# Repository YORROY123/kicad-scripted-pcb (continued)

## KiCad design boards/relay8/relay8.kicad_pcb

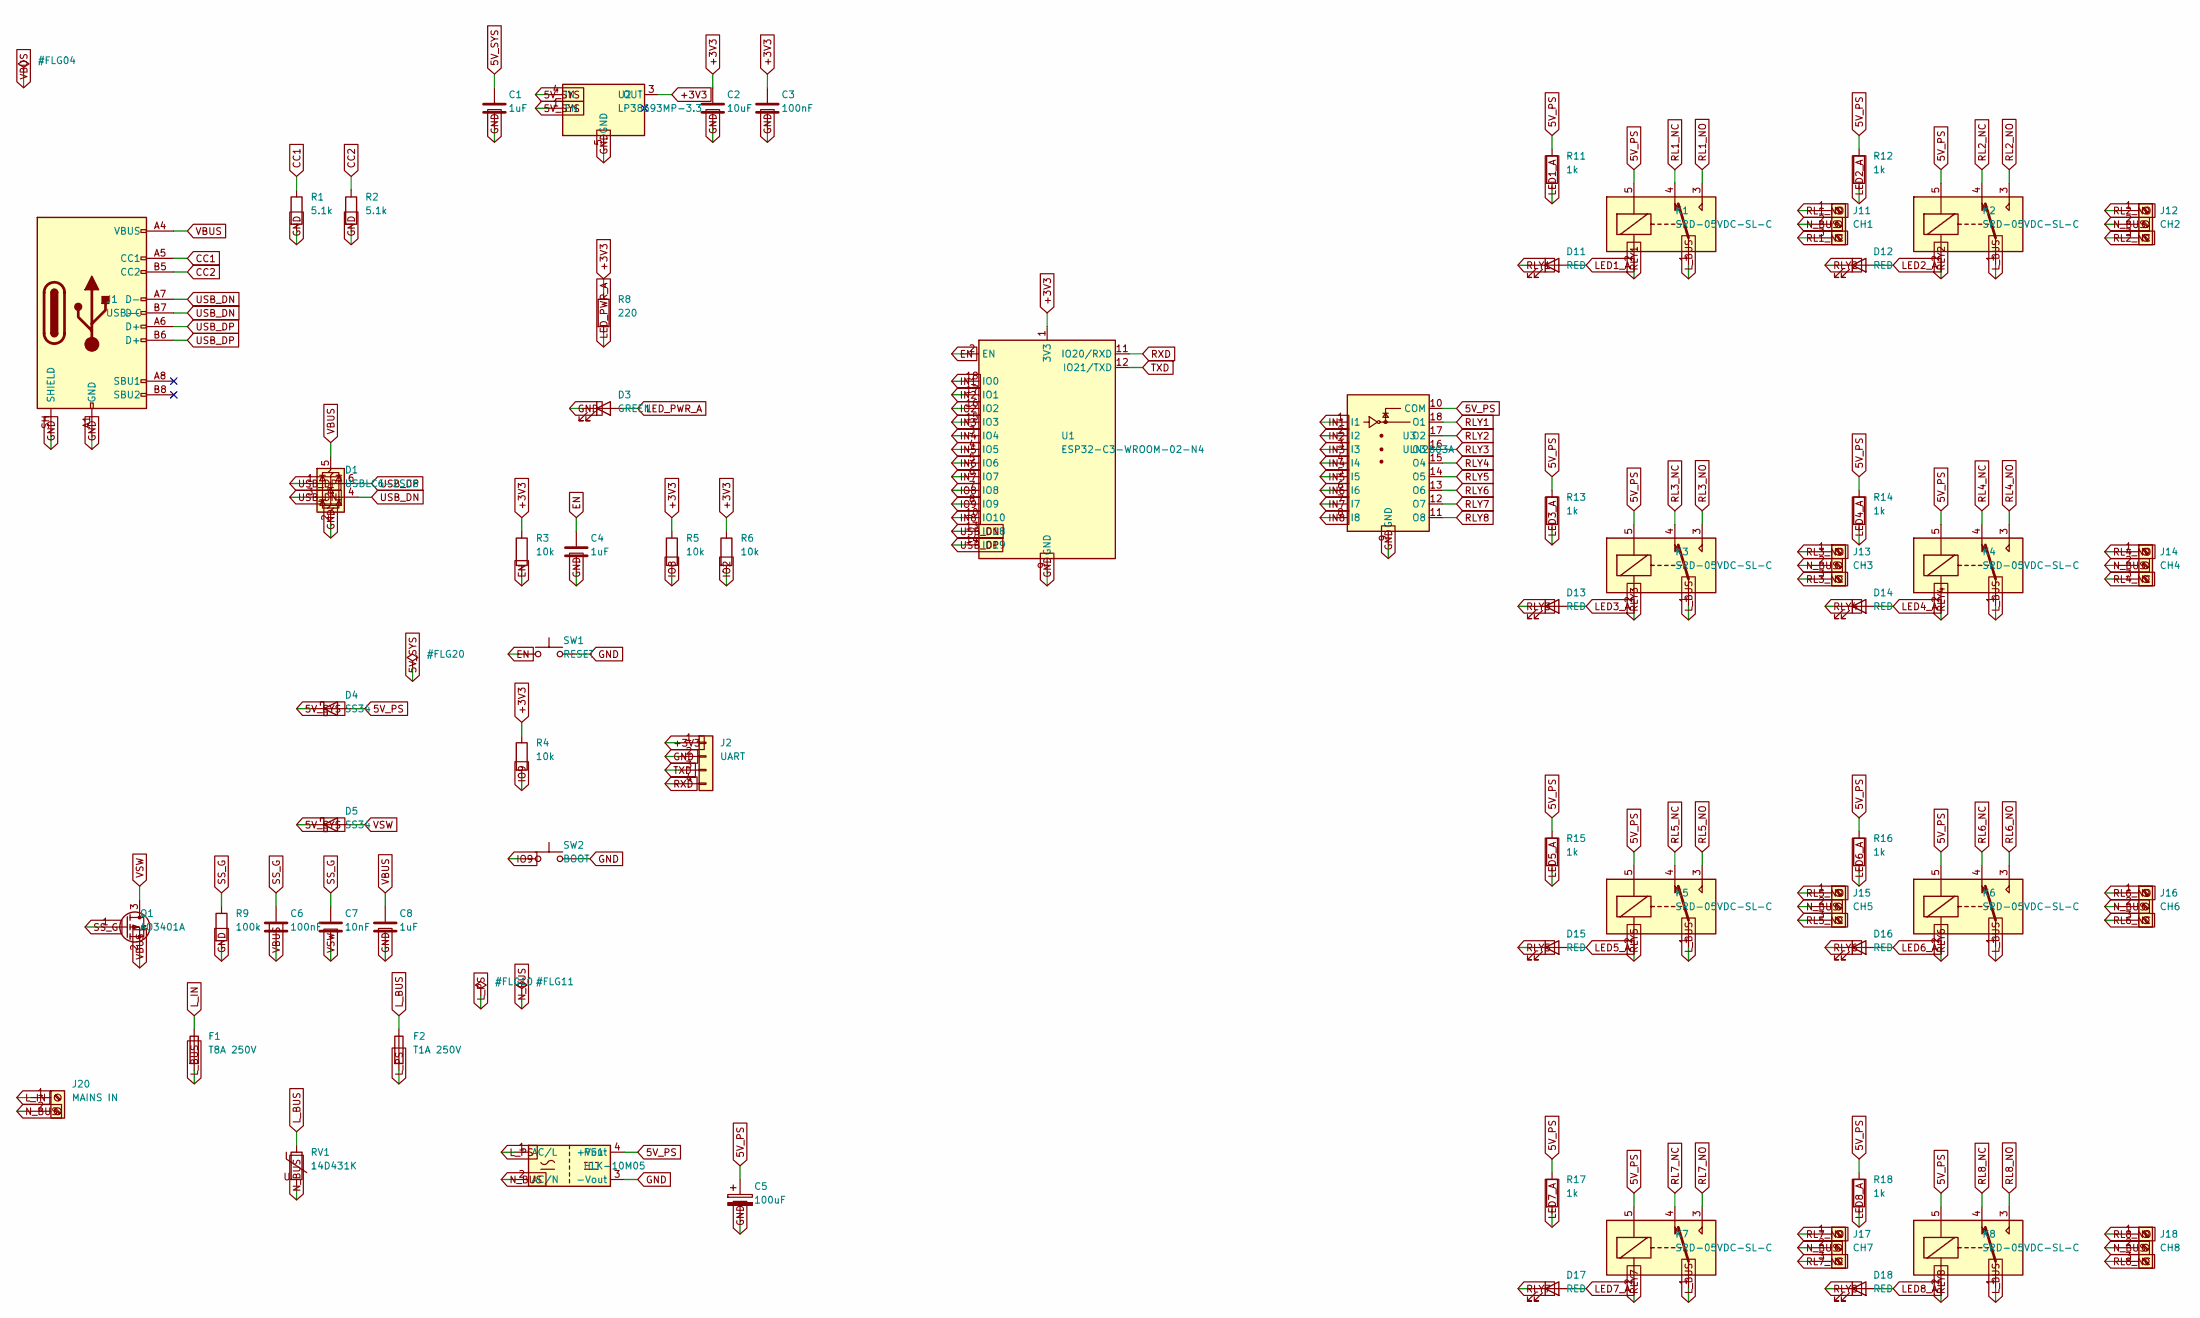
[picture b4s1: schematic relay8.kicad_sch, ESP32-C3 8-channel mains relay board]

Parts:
C1, C4, C8: 1uF; C_0402_1005Metric
C2: 10uF; C_0805_2012Metric
C3, C6: 100nF; C_0402_1005Metric
C5: 100uF; CP_Elec_6.3x7.7
C7: 10nF; C_0402_1005Metric
D1: USBLC6-2SC6; SOT-23-6
D3: GREEN; LED_0805_2012Metric
D4, D5: SS34; D_SMA
D11, D12, D13, D14, D15, D16, D17, D18: RED; LED_0805_2012Metric
F1: T8A 250V; Fuseholder_Clip-5x20mm_Keystone_3517_Inline_P23.11x6.76mm_D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
F2: T1A 250V; Fuseholder_TR5_Littelfuse_No560_No460
J1: USB-C; USB_C_Receptacle_HRO_TYPE-C-31-M-12
J2: UART; PinHeader_1x04_P2.54mm_Vertical
J11: CH1; TerminalBlock_MetzConnect_Type171_RT13703HBWC_1x03_P7.50mm_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
J12: CH2; TerminalBlock_MetzConnect_Type171_RT13703HBWC_1x03_P7.50mm_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
J13: CH3; TerminalBlock_MetzConnect_Type171_RT13703HBWC_1x03_P7.50mm_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
J14: CH4; TerminalBlock_MetzConnect_Type171_RT13703HBWC_1x03_P7.50mm_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
J15: CH5; TerminalBlock_MetzConnect_Type171_RT13703HBWC_1x03_P7.50mm_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
J16: CH6; TerminalBlock_MetzConnect_Type171_RT13703HBWC_1x03_P7.50mm_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
J17: CH7; TerminalBlock_MetzConnect_Type171_RT13703HBWC_1x03_P7.50mm_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
J18: CH8; TerminalBlock_MetzConnect_Type171_RT13703HBWC_1x03_P7.50mm_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
J20: MAINS IN; TerminalBlock_MetzConnect_Type171_RT13702HBWC_1x02_P7.50mm_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
K1, K2, K3, K4, K5, K6, K7, K8: SRD-05VDC-SL-C; Relay_SPDT_SANYOU_SRD_Series_Form_C
PS1: HLK-10M05; Converter_ACDC_Hi-Link_HLK-10Mxx
Q1: AO3401A; SOT-23
R1, R2: 5.1k; R_0402_1005Metric
R3, R4, R5, R6: 10k; R_0402_1005Metric
R8: 220; R_0402_1005Metric
R9: 100k; R_0402_1005Metric
R11, R12, R13, R14, R15, R16, R17, R18: 1k; R_0402_1005Metric
RV1: 14D431K; RV_Disc_D15.5mm_W4.4mm_P7.5mm
SW1: RESET; SW_Push_1P1T_NO_CK_KMR2
SW2: BOOT; SW_Push_1P1T_NO_CK_KMR2
U1: ESP32-C3-WROOM-02-N4; ESP32-C3-WROOM-02
U2: LP38693MP-3.3; SOT-223-5
U3: ULN2803A; SOIC-18W_7.5x11.6mm_P1.27mm

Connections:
5V_PS: C5.1, D4.2 (A), K1.5, K2.5, K3.5, K4.5, K5.5, K6.5, K7.5, K8.5, PS1.4 (+Vout), R11.1, R12.1, R13.1, R14.1, R15.1, R16.1, R17.1, R18.1, U3.10 (COM)
5V_SYS: C1.1, D4.1 (K), D5.1 (K), U2.1 (EN), U2.4 (IN)
+3V3: C2.1, C3.1, J2.1, R3.1, R4.1, R5.1, R6.1, R8.1, U1.1 (3V3), U2.3 (OUT)
CC1: J1.A5 (CC1), R1.1
CC2: J1.B5 (CC2), R2.1
EN: C4.1, R3.2, SW1.1, U1.2 (EN)
GND: C1.2, C2.2, C3.2, C4.2, C5.2, C8.2, D1.2 (GND), D3.1 (K), J1.A1 (GND), J1.A12 (GND), J1.B1 (GND), J1.B12 (GND), J1.SH (SHIELD), J2.2, PS1.3 (-Vout), R1.2, R2.2, R9.2, SW1.2, SW2.2, U1.9 (GND), U1.19 (GND), U2.5 (GND), U3.9 (GND)
IN1: U1.18 (IO0), U3.1 (I1)
IN2: U1.17 (IO1), U3.2 (I2)
IN3: U1.15 (IO3), U3.3 (I3)
IN4: U1.3 (IO4), U3.4 (I4)
IN5: U1.4 (IO5), U3.5 (I5)
IN6: U1.5 (IO6), U3.6 (I6)
IN7: U1.6 (IO7), U3.7 (I7)
IN8: U1.10 (IO10), U3.8 (I8)
IO2: R6.2, U1.16 (IO2)
IO8: R5.2, U1.7 (IO8)
IO9: R4.2, SW2.1, U1.8 (IO9)
LED1_A: D11.2 (A), R11.2
LED2_A: D12.2 (A), R12.2
LED3_A: D13.2 (A), R13.2
LED4_A: D14.2 (A), R14.2
LED5_A: D15.2 (A), R15.2
LED6_A: D16.2 (A), R16.2
LED7_A: D17.2 (A), R17.2
LED8_A: D18.2 (A), R18.2
LED_PWR_A: D3.2 (A), R8.2
L_BUS: F1.2, F2.1, K1.1, K2.1, K3.1, K4.1, K5.1, K6.1, K7.1, K8.1, RV1.1
L_IN: F1.1, J20.1
L_PS: F2.2, PS1.1 (AC/L)
N_BUS: J11.2, J12.2, J13.2, J14.2, J15.2, J16.2, J17.2, J18.2, J20.2, PS1.2 (AC/N), RV1.2
RL1_NC: J11.3, K1.4
RL1_NO: J11.1, K1.3
RL2_NC: J12.3, K2.4
RL2_NO: J12.1, K2.3
RL3_NC: J13.3, K3.4
RL3_NO: J13.1, K3.3
RL4_NC: J14.3, K4.4
RL4_NO: J14.1, K4.3
RL5_NC: J15.3, K5.4
RL5_NO: J15.1, K5.3
RL6_NC: J16.3, K6.4
RL6_NO: J16.1, K6.3
RL7_NC: J17.3, K7.4
RL7_NO: J17.1, K7.3
RL8_NC: J18.3, K8.4
RL8_NO: J18.1, K8.3
RLY1: D11.1 (K), K1.2, U3.18 (O1)
RLY2: D12.1 (K), K2.2, U3.17 (O2)
RLY3: D13.1 (K), K3.2, U3.16 (O3)
RLY4: D14.1 (K), K4.2, U3.15 (O4)
RLY5: D15.1 (K), K5.2, U3.14 (O5)
RLY6: D16.1 (K), K6.2, U3.13 (O6)
RLY7: D17.1 (K), K7.2, U3.12 (O7)
RLY8: D18.1 (K), K8.2, U3.11 (O8)
RXD: J2.4, U1.11 (IO20/RXD)
SS_G: C6.1, C7.1, Q1.1 (G), R9.1
TXD: J2.3, U1.12 (IO21/TXD)
USB_DN: D1.3 (I/O2), D1.4 (I/O2), J1.A7 (D-), J1.B7 (D-), U1.13 (IO18)
USB_DP: D1.1 (I/O1), D1.6 (I/O1), J1.A6 (D+), J1.B6 (D+), U1.14 (IO19)
VBUS: C6.2, C8.1, D1.5 (VBUS), J1.A4 (VBUS), J1.A9 (VBUS), J1.B4 (VBUS), J1.B9 (VBUS), Q1.2 (S)
VSW: C7.2, D5.2 (A), Q1.3 (D)

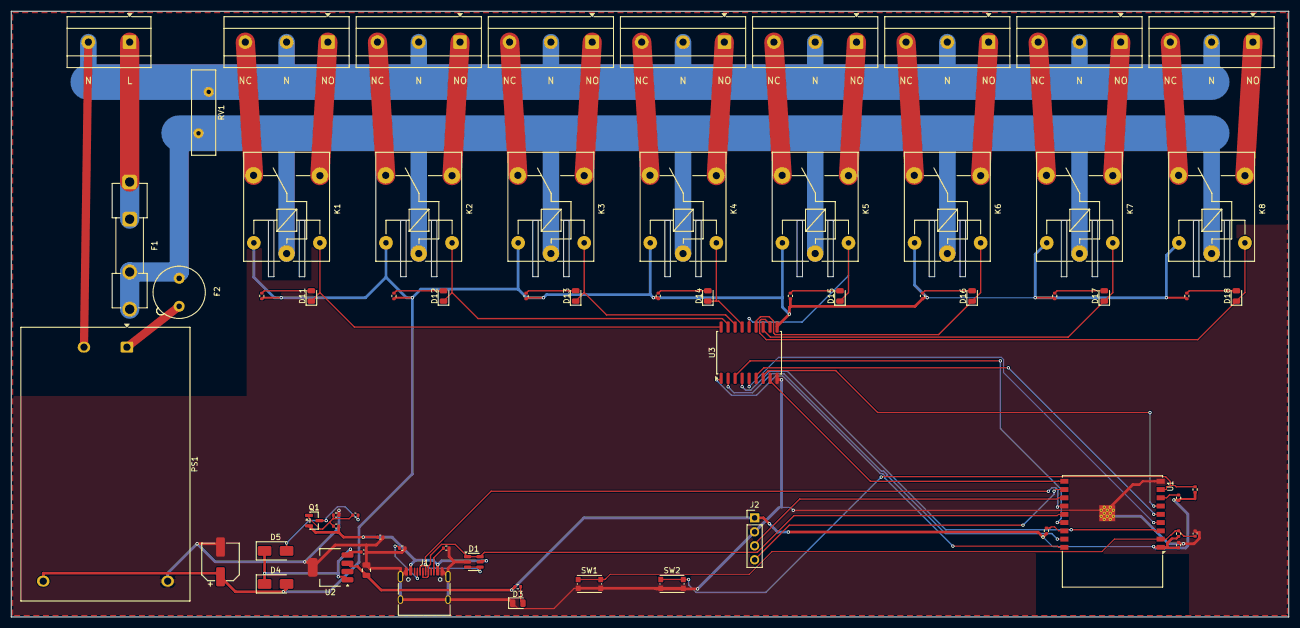
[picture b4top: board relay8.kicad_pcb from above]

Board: 2 copper layers, 232.0 x 110.0 mm, 65 parts (0 on the bottom side), 62 nets.

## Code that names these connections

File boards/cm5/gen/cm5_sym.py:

"""Raspberry Pi Compute Module 5 的符號:兩顆 100 腳 DF40 各一個符號(CM5_J1、CM5_J2)。

KiCad 10 的 MCU_Module 只到 CM3,CM4/CM5 都沒有,所以自己畫。

腳位表照抄《Raspberry Pi Compute Module 5 datasheet》4.2 Pinout(cm5-datasheet.pdf)。
`--verify <datasheet 文字檔>` 會從 pdftotext -layout 的輸出重新解析一次,逐腳比對;
規格書不放進 repo(版權),所以預設不跑,改腳位表時一定要跑。

焊盤編號:CM5 的 1–100 腳在第一顆連接器、101–200 在第二顆。符號腳號就是焊盤號
(1–100),CM5_J2 的焊盤 n = CM5 第 100+n 腳。腳名保留規格書原名,J2 另外在名稱後面
不加註 —— 要看 CM5 腳號就 +100。
封裝 CM5:Amphenol_10164227-1001A1RLF_2x50_P0.4mm 由 cm5_fp.py 生成:焊盤 n = CM5 腳 n
(J2 為 100+n),已用 --compare 對官方 CM5 IO Board 封裝逐焊盤確認(200/200)。

用法: python cm5_sym.py [--verify cm5.txt]  → 寫 ../symbols/CM5.kicad_sym
"""
from __future__ import annotations

import re
import sys
from pathlib import Path

HERE = Path(__file__).resolve().parent
OUT = HERE.parent / "symbols" / "CM5.kicad_sym"

# CM5 腳 1..200 的名稱,照規格書順序,每列 10 腳
PINOUT = """
GND GND Ethernet_Pair3_P Ethernet_Pair1_P Ethernet_Pair3_N Ethernet_Pair1_N GND GND Ethernet_Pair2_N Ethernet_Pair0_N
Ethernet_Pair2_P Ethernet_Pair0_P GND GND Ethernet_nLED3 Fan_Tacho Ethernet_nLED2 Ethernet_SYNC_OUT Fan_PWM EEPROM_nWP
LED_nACT GND GND GPIO26 GPIO21 GPIO19 GPIO20 GPIO13 GPIO16 GPIO6
GPIO12 GND GND GPIO5 ID_SC ID_SD GPIO7 GPIO11 GPIO8 GPIO9
GPIO25 GND GND GPIO10 GPIO24 GPIO22 GPIO23 GPIO27 GPIO18 GPIO17
GPIO15 GND GND GPIO4 GPIO14 GPIO3 SD_CLK GPIO2 GND GND
SD_DAT3 SD_CMD SD_DAT0 SD_DAT5 GND GND SD_DAT1 SD_DAT4 SD_DAT2 SD_DAT7
GND SD_DAT6 SD_VDD_OVERRIDE GND SD_PWR_ON VBAT 5V GPIO_VREF 5V SCL0
5V SDA0 5V CM5_3.3V 5V CM5_3.3V 5V CM5_1.8V WL_nDisable CM5_1.8V
BT_nDisable PWR_Button nRPIBOOT CC1 LED_nPWR CC2 CAM_GPIO0 GND PMIC_Enable CAM_GPIO1
USB_OTG_ID PCIe_CLK_nREQ USB_N PCIE_nWAKE USB_P PCIE_PWR_EN GND GND PCIe_nRST PCIe_CLK_P
VBUS_EN PCIe_CLK_N GND GND MIPI0_D0_N PCIe_RX_P MIPI0_D0_P PCIe_RX_N GND GND
MIPI0_D1_N PCIe_TX_P MIPI0_D1_P PCIe_TX_N GND GND MIPI0_C_N USB3-0-RX_N MIPI0_C_P USB3-0-RX_P
GND GND MIPI0_D2_N USB3-0-DP MIPI0_D2_P USB3-0-DM GND GND MIPI0_D3_N USB3-0-TX_N
MIPI0_D3_P USB3-0-TX_P HDMI1_HOTPLUG GND HDMI1_SDA HDMI1_TX2_P HDMI1_SCL HDMI1_TX2_N HDMI1_CEC GND
HDMI0_CEC HDMI1_TX1_P HDMI0_HOTPLUG HDMI1_TX1_N GND GND USB3-1-RX_N HDMI1_TX0_P USB3-1-RX_P HDMI1_TX0_N
GND GND USB3-1-DP HDMI1_CLK_P USB3-1-DM HDMI1_CLK_N GND GND USB3-1-TX_N HDMI0_TX2_P
USB3-1-TX_P HDMI0_TX2_N GND GND MIPI1_D0_N HDMI0_TX1_P MIPI1_D0_P HDMI0_TX1_N GND GND
MIPI1_D1_N HDMI0_TX0_P MIPI1_D1_P HDMI0_TX0_N GND GND MIPI1_C_N HDMI0_CLK_P MIPI1_C_P HDMI0_CLK_N
GND GND MIPI1_D2_N MIPI1_D3_N MIPI1_D2_P MIPI1_D3_P GND GND HDMI0_SDA HDMI0_SCL
""".split()
assert len(PINOUT) == 200, len(PINOUT)
NAME = {i + 1: n for i, n in enumerate(PINOUT)}


def etype(name: str, pin: int = 0) -> str:
    """ERC 用的電氣類型。電源腳照方向給,其餘一律 passive(避免 input 沒驅動的假警告)。"""
    if name in ("GND", "5V", "GPIO_VREF", "VBAT"):
        return "power_in"
    if name in ("CM5_3.3V", "CM5_1.8V"):
        # 每路兩支腳(84/86、88/90)是同一個輸出;兩支都標 power_out,ERC 會當成兩個電源互接
        return "power_out" if pin in (84, 88) else "passive"
    if name in ("LED_nPWR", "LED_nACT", "Ethernet_nLED2", "Ethernet_nLED3"):   # 模組內是開汲極拉低(VOL < 0.4V),review.py 的 led-current 要知道
        return "open_collector"
    return "passive"


def verify(txt: Path) -> int:
    """從規格書文字檔(pdftotext -layout -enc UTF-8)的 4.2 Pinout 重新解析,逐腳比對。"""
    lines = txt.read_text(encoding="utf-8").splitlines()
    start = next(i for i, s in enumerate(lines) if re.match(r"^\s*4\.2\. Pinout\s*$", s))
    got: dict[int, str] = {}
    for s in lines[start:start + 600]:
        m = re.match(r"^\s*(\d{1,3})\s+(\S+)\s", s + " ")
        if m and 1 <= int(m.group(1)) <= 200 and int(m.group(1)) not in got:
            got[int(m.group(1))] = m.group(2)
    bad = [n for n in range(1, 201) if got.get(n) != NAME[n]]
    for n in bad:
        print(f"  腳 {n}: 表={NAME[n]} 規格書={got.get(n)}")
    print(f"verify: {200 - len(bad)}/200 一致")
    return 1 if bad else 0


def font() -> str:
    return "(effects\n\t\t\t\t\t\t(font\n\t\t\t\t\t\t\t(size 1.27 1.27)\n\t\t\t\t\t\t)\n\t\t\t\t\t)"


def prop(key: str, val: str, x: float, y: float, hide: bool) -> str:
    h = "\n\t\t\t(hide yes)" if hide else ""
    return (f'\t\t(property "{key}" "{val}"\n\t\t\t(at {x} {y} 0)\n\t\t\t(show_name no)\n'
            f'\t\t\t(do_not_autoplace no){h}\n\t\t\t(effects\n\t\t\t\t(font\n\t\t\t\t\t(size 1.27 1.27)\n'
            f'\t\t\t\t)\n\t\t\t\t(justify left)\n\t\t\t)\n\t\t)\n')


P = 2.54
HALF_W = 25.4          # 本體半寬:兩側腳名最長 17 字,約 17 mm,中間留空
ROWS = 50


def symbol(sym: str, first: int, desc: str) -> str:
    top = (ROWS - 1) / 2 * P            # 第一列 y
    body_h = top + P
    out = [f'\t(symbol "{sym}"\n\t\t(pin_names\n\t\t\t(offset 0.762)\n\t\t)\n'
           "\t\t(exclude_from_sim no)\n\t\t(in_bom yes)\n\t\t(on_board yes)\n\t\t(in_pos_files yes)\n"
           "\t\t(duplicate_pin_numbers_are_jumpers no)\n"]
    out.append(prop("Reference", "J", -HALF_W, round(body_h + P, 2), False))
    out.append(prop("Value", sym, 0, round(body_h + P, 2), False))
    out.append(prop("Footprint", "CM5:Amphenol_10164227-1001A1RLF_2x50_P0.4mm", 0, 0, True))
    out.append(prop("Datasheet", "https://datasheets.raspberrypi.com/cm5/cm5-datasheet.pdf", 0, 0, True))
    out.append(prop("Description", desc, 0, 0, True))
    out.append(f'\t\t(symbol "{sym}_0_1"\n\t\t\t(rectangle\n\t\t\t\t(start {-HALF_W} {body_h})\n'
               f"\t\t\t\t(end {HALF_W} {-body_h})\n\t\t\t\t(stroke\n\t\t\t\t\t(width 0.254)\n"
               "\t\t\t\t\t(type default)\n\t\t\t\t)\n\t\t\t\t(fill\n\t\t\t\t\t(type background)\n"
               "\t\t\t\t)\n\t\t\t)\n\t\t)\n")
    out.append(f'\t\t(symbol "{sym}_1_1"\n')
    for pad in range(1, 101):
        name = NAME[first + pad - 1]
        row = (pad - 1) // 2
        y = round(top - row * P, 2)
        x, ang = (-(HALF_W + P), 0) if pad % 2 else (HALF_W + P, 180)
        out.append(f"\t\t\t(pin {etype(name, first + pad - 1)} line\n\t\t\t\t(at {x} {y} {ang})\n\t\t\t\t(length {P})\n"
                   f'\t\t\t\t(name "{name}"\n\t\t\t\t\t{font()}\n\t\t\t\t)\n'
                   f'\t\t\t\t(number "{pad}"\n\t\t\t\t\t{font()}\n\t\t\t\t)\n\t\t\t)\n')
    out.append("\t\t)\n\t\t(embedded_fonts no)\n\t)\n")
    return "".join(out)


def main() -> int:
    if "--verify" in sys.argv:
        rc = verify(Path(sys.argv[sys.argv.index("--verify") + 1]))
        if rc:
            return rc
    text = ("(kicad_symbol_lib\n\t(version 20251024)\n\t(generator \"kicad-scripted-pcb\")\n"
            + symbol("CM5_J1", 1, "Raspberry Pi CM5, connector 1 (CM5 pins 1-100)")
            + symbol("CM5_J2", 101, "Raspberry Pi CM5, connector 2 (pad n = CM5 pin 100+n)")
            + ")\n")
    OUT.parent.mkdir(parents=True, exist_ok=True)
    OUT.write_text(text, encoding="utf-8", newline="\n")
    print(f"wrote {OUT}")
    return 0


if __name__ == "__main__":
    sys.exit(main())

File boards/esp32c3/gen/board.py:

"""ESP32-C3 最小系统板:USB-C 供电 + 原生 USB 下载/调试 + 3.3V LDO + 按键 + LED + 排针。

依据 Espressif《ESP32-C3 硬件设计指南》与 ESP32-C3-WROOM-02 规格书:
  - USB D-/D+ 直连 GPIO18/GPIO19(芯片内置 USB Serial/JTAG,不需要 USB 转串口芯片)
  - EN:10k 上拉 + 1µF 对地(上电复位延时),RESET 键把 EN 拉低
  - GPIO9 是启动模式脚:上拉 = 从 flash 启动;按住 BOOT 键(拉低)上电 = 下载模式
  - GPIO2、GPIO8 是 strapping 脚,上电时须为高,各 10k 上拉
  - 用户 LED 接 GPIO10(不是 strapping 脚,接 LED 不影响启动)

电源吸取 usbc-ldo 那块板子的模拟教训(见 AGENTS.md):
  - 不串二极管、LDO 用 LP38693MP-3.3(壓差 ~330mV @0.5A;輸入耐壓 12V,扛得住熱插拔過衝)
  - 插入浪湧:模組內部還有約 12.3µF,直接接 VBUS 會灌進約 79µC(> USB 2.0 的 50µC)
    → 加 P-MOSFET 軟啟動(Q1,見下方與 sim/softstart_sim.py)

画法:网络标签式。每个引脚沿「离开器件」的方向拉 2.54mm 短线挂一个全局标签,
电路本身就是下面那张「引脚 → 网络」对照表,审查时逐行对 datasheet 即可。
"""
import json
import math
import sys
from pathlib import Path

HERE = Path(__file__).resolve().parent
SHARED = HERE.parents[2] / "lib"
sys.path.insert(0, str(SHARED))
from schgen import Part, Schematic  # noqa: E402

G = 1.27
STUB = 2 * G


def g(n: float) -> float:
    return round(n * G, 4)


s = Schematic(title="ESP32-C3 minimal board (USB-C, native USB)")


def outward(part: Part, pin: str) -> tuple[float, float]:
    """引脚「离开器件」的单位方向(图纸坐标,y 向下)。

    符号库里引脚的 angle 指向器件本体;反过来就是向外。还要套上器件的旋转。
    """
    part.pin_xy(pin)                       # 确保 _pins 已载入
    a = math.radians(part._pins[pin]["angle"] + 180)
    vx, vy = math.cos(a), -math.sin(a)     # 符号库 y 向上 → 图纸 y 向下
    r = math.radians(part.rotation)
    rx = vx * math.cos(r) - vy * math.sin(r)
    ry = vx * math.sin(r) + vy * math.cos(r)
    return round(rx), round(ry)


# 标签朝向:文字顺着短线方向往外长,不压在器件上
LABEL_ROT = {(1, 0): 0, (-1, 0): 180, (0, -1): 90, (0, 1): 270}

# 设计意图:每个引脚应接到哪个网(None = 刻意不接)。写成 JSON 交给 check_netlist.py
# 和 kicad-cli 导出的网表逐脚比对 —— ERC 默认不报「全局标签只出现一次」,
# 标签名打错字会变成一个孤立的网,只有比对网表才抓得到。
EXPECTED: dict = {}


def attach(part: Part, pins: dict) -> Part:
    """按「引脚 → 网络」接线;网络为 None 表示刻意不接(打 NC 记号)。

    同一坐标上的堆叠引脚(USB-C 的 A4/A9/B4/B9 等)只挂一次标签。
    """
    seen = set()
    for pin, net in pins.items():
        if not part.ref.startswith("#"):
            EXPECTED[f"{part.ref}.{pin}"] = net
        xy = part.pin_xy(pin)
        if xy in seen:
            continue
        seen.add(xy)
        if net is None:
            s.no_connect(part, pin)
            continue
        ox, oy = outward(part, pin)
        s.label(net, part, pin, dx=ox * STUB, dy=oy * STUB, rotation=LABEL_ROT[(ox, oy)])
    return part


def add(ref, lib, name, x, y, value, footprint, pins, rot=0.0):
    p = s.add(Part(ref, lib, name, g(x), g(y), value=value, footprint=footprint, rotation=rot))
    return attach(p, pins)


def flag(net: str, x: float, y: float) -> None:
    """PWR_FLAG:告诉 ERC 这个网确实由外部供电(USB 进来的 VBUS、以及 GND)。"""
    p = s.add(Part(f"#FLG{len(s.parts):02d}", "power", "PWR_FLAG", g(x), g(y),
                   value="PWR_FLAG", fields_hidden=True))
    attach(p, {"1": net})


R0402 = "Resistor_SMD:R_0402_1005Metric"
C0402 = "Capacitor_SMD:C_0402_1005Metric"
C0805 = "Capacitor_SMD:C_0805_2012Metric"
LED0805 = "LED_SMD:LED_0805_2012Metric"
BUTTON = "Button_Switch_SMD:SW_Push_1P1T_NO_CK_KMR2"

# ── USB-C 输入 ──────────────────────────────────────────────────────────
add("J1", "Connector", "USB_C_Receptacle_USB2.0_16P", 30, 60, "USB-C",
    "Connector_USB:USB_C_Receptacle_HRO_TYPE-C-31-M-12", {
        "A4": "VBUS", "A9": "VBUS", "B4": "VBUS", "B9": "VBUS",
        "A1": "GND", "A12": "GND", "B1": "GND", "B12": "GND", "SH": "GND",
        "A5": "CC1", "B5": "CC2",
        # USB-C 正反插:A、B 两面的 D+/D- 在这里并到同一个网
        "A6": "USB_DP", "B6": "USB_DP", "A7": "USB_DN", "B7": "USB_DN",
        "A8": None, "B8": None,          # SBU 本设计不用
    })
# CC 各 5.1k 下拉:告诉 USB-C 供电端「我是设备,给我 5V」
add("R1", "Device", "R", 60, 50, "5.1k", R0402, {"1": "CC1", "2": "GND"})
add("R2", "Device", "R", 68, 50, "5.1k", R0402, {"1": "CC2", "2": "GND"})
# ESD:USBLC6 的 1/6、3/4 是同一条线的两端(穿过式),VBUS 脚做钳位参考
add("D1", "Power_Protection", "USBLC6-2SC6", 64, 80, "USBLC6-2SC6",
    "Package_TO_SOT_SMD:SOT-23-6", {
        "1": "USB_DP", "6": "USB_DP", "3": "USB_DN", "4": "USB_DN",
        "5": "VBUS", "2": "GND",
    })
flag("VBUS", 20, 30)
flag("GND", 28, 30)

# ── 3.3V LDO ───────────────────────────────────────────────────────────
# LP38693MP-3.3(TI SNVS321O):輸入絕對最大 12V、壓差 330mV @0.5A、額定 500mA。
# 原本用 AP2112K(絕對最大 6.5V),但 VBUS 只有 1µF 時熱插拔過衝模擬到 8.6V
# (sim/power_sim.py)。500mA 剛好滿足模組規格書「外部電源 ≥0.5A」。
add("U2", "Regulator_Linear", "LP38693MP-3.3", 100, 30, "LP38693MP-3.3",
    "Package_TO_SOT_SMD:SOT-223-5", {
        "4": "VSW", "1": "VSW",          # EN 接 IN:軟啟動後的電源一到就輸出(折返限流此時有效)
        "5": "GND", "3": "+3V3", "2": None,
    })
add("C1", "Device", "C", 82, 30, "1uF", C0402, {"1": "VBUS", "2": "GND"})
add("C2", "Device", "C", 118, 30, "10uF", C0805, {"1": "+3V3", "2": "GND"})
add("C3", "Device", "C", 126, 30, "100nF", C0402, {"1": "+3V3", "2": "GND"})

# ── VBUS 軟啟動(sim/softstart_sim.py)───────────────────────────────────
# 模組內部約 12.3µF + C2 10µF 掛在 LDO 後面,直接接 VBUS 插入時灌進約 79µC,
# 超過 USB 2.0 的 50µC(10µF 等效)。P-MOSFET 串在 VBUS 與 LDO 之間:
#   插入瞬間 C6 把閘極綁在源極 → 先關著;R9 慢慢把閘極拉向地 → 逐漸導通;
#   C7(閘-汲)讓輸出等斜率爬升:爬升段電流 80–97mA(Vth −0.5…−1.3V),3V3 1.3–3.7ms 就緒。
# AO3401A(AOS Rev 3.1):VDS −30V、VGS ±12V、RDS(on) <60mΩ @ −4.5V。
# 限制:拔掉後 C6 經 R9 放電(時間常數 10ms),拔插間隔太短時軟啟動不完整。
add("Q1", "Transistor_FET", "AO3401A", 100, 10, "AO3401A",
    "Package_TO_SOT_SMD:SOT-23", {"1": "SS_G", "2": "VBUS", "3": "VSW"})
add("R9", "Device", "R", 140, 10, "100k", R0402, {"1": "SS_G", "2": "GND"})
add("C6", "Device", "C", 148, 10, "100nF", C0402, {"1": "SS_G", "2": "VBUS"})
add("C7", "Device", "C", 156, 10, "10nF", C0402, {"1": "SS_G", "2": "VSW"})
add("C5", "Device", "C", 164, 10, "1uF", C0402, {"1": "VSW", "2": "GND"})
# VSW 只經 MOSFET(passive)進來,ERC 會判 LDO 的 power_in 未被驅動;這裡確實是電源入口
flag("VSW", 172, 10)

# ── ESP32-C3 模块 ──────────────────────────────────────────────────────
add("U1", "RF_Module", "ESP32-C3-WROOM-02", 170, 80, "ESP32-C3-WROOM-02-N4",
    "RF_Module:ESP32-C3-WROOM-02", {
        "1": "+3V3", "9": "GND", "19": "GND",
        "2": "EN",
        "8": "IO9",                      # BOOT
        "7": "IO8", "16": "IO2",         # strapping,上拉
        "13": "USB_DN", "14": "USB_DP",  # GPIO18 = D-,GPIO19 = D+
        "11": "RXD", "12": "TXD",
        "10": "LED_USER",
        "3": "IO4", "4": "IO5", "5": "IO6", "6": "IO7",
        "18": None, "17": None, "15": None,   # IO0 / IO1 / IO3 未引出
    })

# ── 复位与启动 ──────────────────────────────────────────────────────────
add("R3", "Device", "R", 110, 70, "10k", R0402, {"1": "+3V3", "2": "EN"})
add("C4", "Device", "C", 118, 70, "1uF", C0402, {"1": "EN", "2": "GND"})
add("SW1", "Switch", "SW_Push", 112, 88, "RESET", BUTTON, {"1": "EN", "2": "GND"})
add("R4", "Device", "R", 110, 110, "10k", R0402, {"1": "+3V3", "2": "IO9"})
add("SW2", "Switch", "SW_Push", 112, 128, "BOOT", BUTTON, {"1": "IO9", "2": "GND"})
add("R5", "Device", "R", 226, 50, "10k", R0402, {"1": "+3V3", "2": "IO8"})
add("R6", "Device", "R", 234, 50, "10k", R0402, {"1": "+3V3", "2": "IO2"})

# ── LED ────────────────────────────────────────────────────────────────
# Device:LED 是 1 = K(阴极)、2 = A(阳极)—— usbc-ldo 那块第一版就接反过,这里写死脚名
# LED 電流由 lib/review.py 檢查:藍光 Vf 2.5–3.6V,接 3.3V GPIO 幾乎不亮 → 改黃光;
# 綠光 Vf 2.6–3.1V,經 1k 只有約 0.45mA → 電阻改 220Ω(約 2mA)。
add("R7", "Device", "R", 226, 110, "470", R0402, {"1": "LED_USER", "2": "LED_USER_A"})
add("D2", "Device", "LED", 226, 128, "KT-0805Y", LED0805, {"2": "LED_USER_A", "1": "GND"})
add("R8", "Device", "R", 82, 110, "220", R0402, {"1": "+3V3", "2": "LED_PWR_A"})
add("D3", "Device", "LED", 82, 128, "GREEN", LED0805, {"2": "LED_PWR_A", "1": "GND"})

# ── 排针 ───────────────────────────────────────────────────────────────
add("J2", "Connector_Generic", "Conn_01x08", 250, 90, "IO",
    "Connector_PinHeader_2.54mm:PinHeader_1x08_P2.54mm_Vertical", {
        "1": "+3V3", "2": "GND", "3": "TXD", "4": "RXD",
        "5": "IO4", "6": "IO5", "7": "IO6", "8": "IO7",
    })

# ── 写出前自检 ─────────────────────────────────────────────────────────
bad = s.crossing_pins() + s.overlapping_wires()
if bad:
    print(f"!! 自检失败 {len(bad)} 项,拒绝写出:")
    for b in bad:
        print("   ", b)
    raise SystemExit(1)

(HERE.parent / "expected_nets.json").write_text(
    json.dumps(EXPECTED, indent=1, ensure_ascii=False, sort_keys=True), encoding="utf-8")
out = HERE.parent / "esp32c3.kicad_sch"
out.write_text(s.render(), encoding="utf-8", newline="\n")
print(f"wrote {out.name}: {len(s.parts)} parts, {len(s.labels)} labels")

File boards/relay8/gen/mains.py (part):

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SLOT_X = (2.3, 3.3)     # 槽相对 COM 的 x 范围(两侧对称),宽 1mm
SLOT_Y = (-6.0, 4.2)    # 槽相对 COM 的 y 范围:上端超过线圈焊盘,下端超过 COM 焊盘

LABELS = {"N_BUS": "N", "L_IN": "L"}    # 其余网取最后一段:RL3_NO → "NO"


def mm(v: float) -> int:
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        xs.append(com[0])
        segs.append((com, (com[0], l_y), "L_BUS", RISER_W, B))                    # COM → L_BUS
        npin = pad_xy(term, "2")
        segs.append((npin, (npin[0], n_y), "N_BUS", RISER_W, B))                  # 端子 N → N_BUS
        for relay_pin, term_pin in (("3", "1"), ("4", "3")):                      # NO、NC
            net = _net_of(relay, relay_pin)
            assert net == _net_of(term, term_pin), (relay.GetReference(), relay_pin)
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        b = (pcbnew.ToMM(c1.GetPosition().x), pcbnew.ToMM(c1.GetPosition().y))
        segs.append((a, b, c0.GetNetname(), INPUT_W, B))
    # RV1 的两个脚放在两条汇流排上,焊盘本身压在汇流排铜上即连通,不另拉线
    for pin, net in (("1", "L_BUS"), ("2", "N_BUS")):
        assert _net_of(rv1, pin) == net, ("RV1", pin)

    for a, b, net, width, layer in segs:
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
